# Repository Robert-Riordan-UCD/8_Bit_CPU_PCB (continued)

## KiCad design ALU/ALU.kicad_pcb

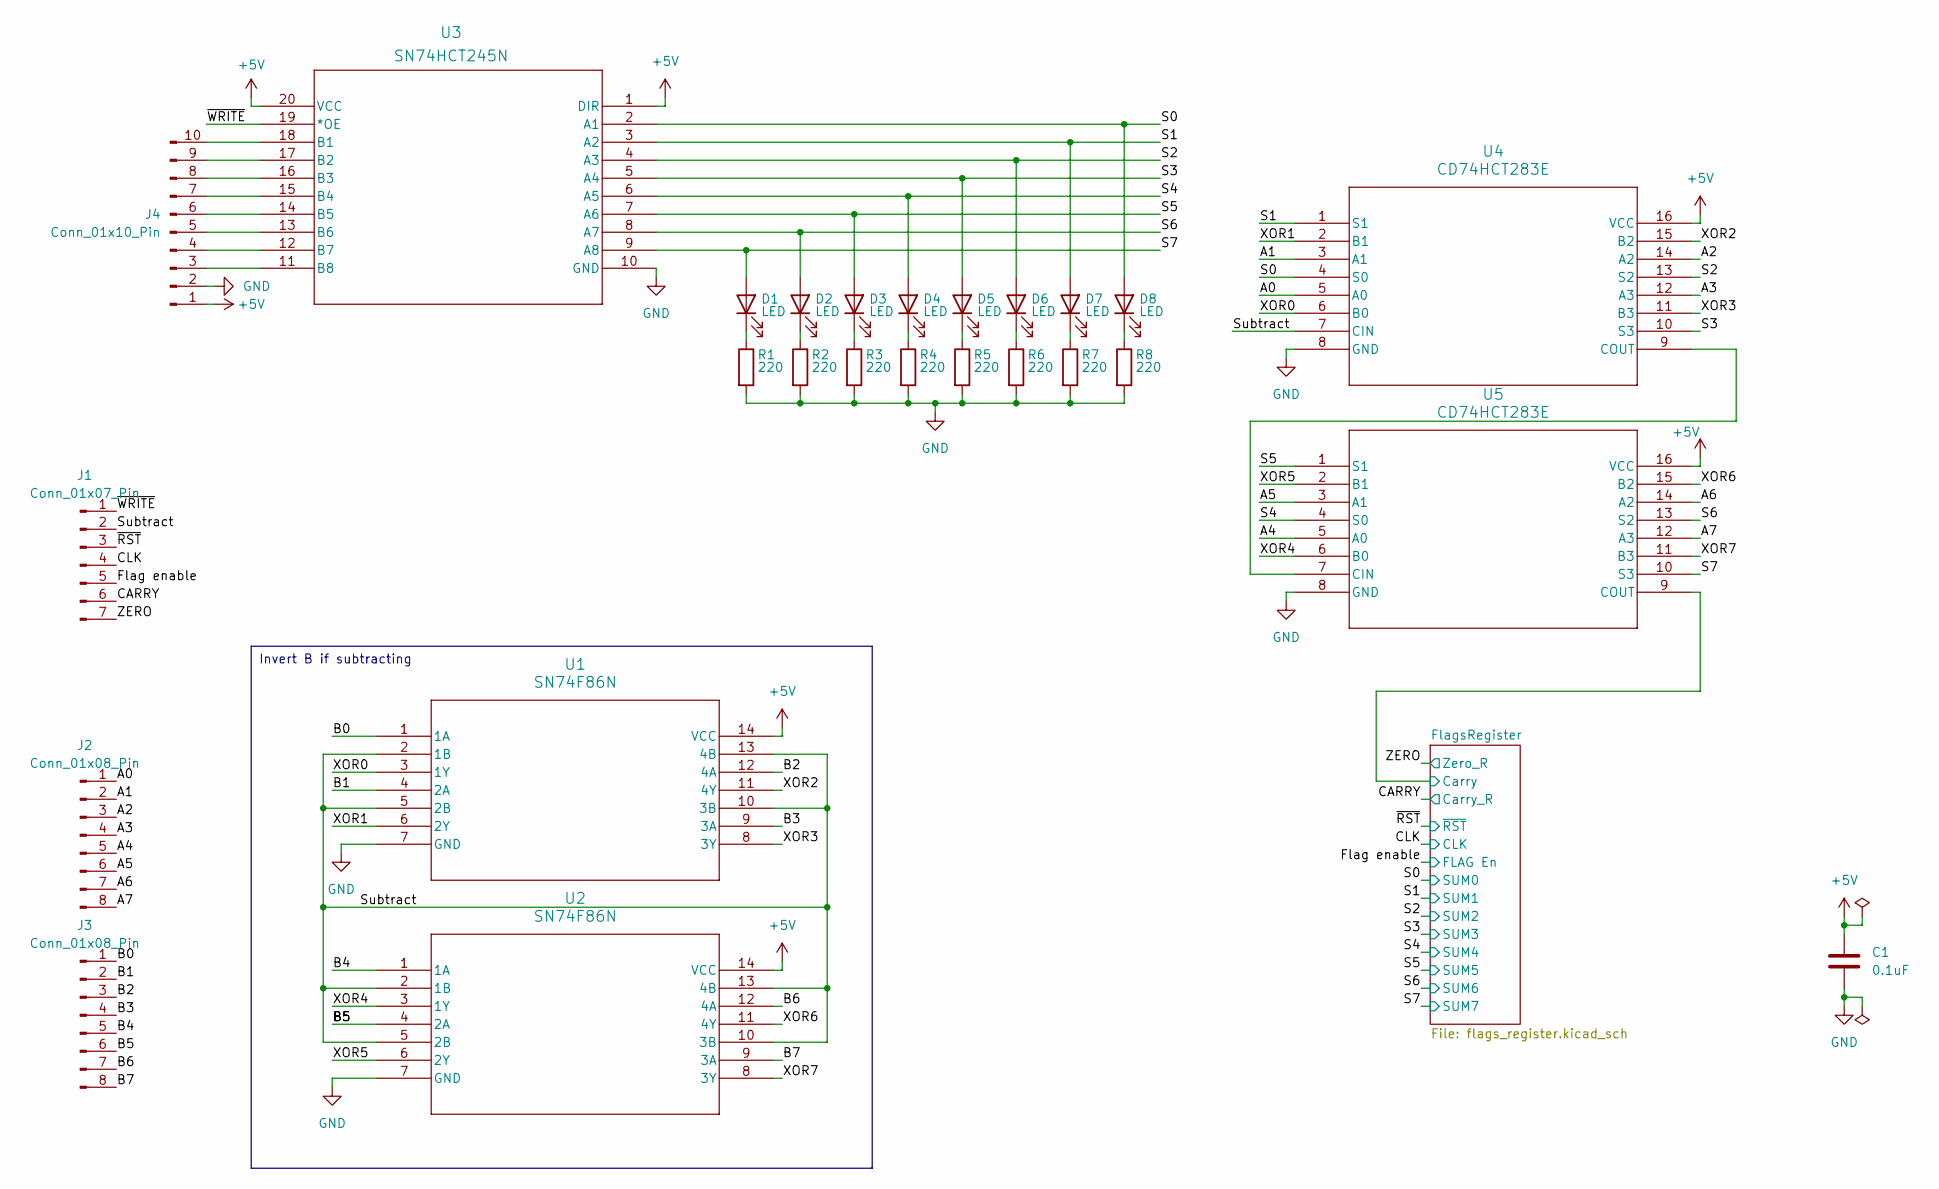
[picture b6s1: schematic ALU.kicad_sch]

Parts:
C1: 0.1uF; C_Disc_D5.0mm_W2.5mm_P2.50mm
D1, D2, D3, D4, D5, D6, D7, D8: LED; LED_D5.0mm
J1: Conn_01x07_Pin; PinHeader_1x07_P2.54mm_Vertical
J2, J3: Conn_01x08_Pin; PinHeader_1x08_P2.54mm_Vertical
J4: Conn_01x10_Pin; PinHeader_1x10_P2.54mm_Vertical
R1, R2, R3, R4, R5, R6, R7, R8: 220; CF_series_Resistors_THT
U1, U2: SN74F86N; 4x_xor
U3: SN74HCT245N; 8x_tristate_transceiver
U4, U5: CD74HCT283E; 4bit_full_adder

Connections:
+5V: C1.1, J4.1, U1.14 (VCC), U2.14 (VCC), U3.1 (DIR), U3.20 (VCC), U4.16 (VCC), U5.16 (VCC); also elsewhere on the board
/A0: J2.1, U4.5 (A0)
/A1: J2.2, U4.3 (A1)
/A2: J2.3, U4.14 (A2)
/A3: J2.4, U4.12 (A3)
/A4: J2.5, U5.5 (A0)
/A5: J2.6, U5.3 (A1)
/A6: J2.7, U5.14 (A2)
/A7: J2.8, U5.12 (A3)
/B0: J3.1, U1.1 (1A)
/B1: J3.2, U1.4 (2A)
/B2: J3.3, U1.12 (4A)
/B3: J3.4, U1.9 (3A)
/B4: J3.5, U2.1 (1A)
/B5: J3.6, U2.4 (2A)
/B6: J3.7, U2.12 (4A)
/B7: J3.8, U2.9 (3A)
/CARRY: J1.6; also elsewhere on the board
/CLK: J1.4; also elsewhere on the board
/Flag enable: J1.5; also elsewhere on the board
/FlagsRegister/Carry: U5.9 (COUT); also elsewhere on the board
/S0: D8.2 (A), U3.2 (A1), U4.4 (S0); also elsewhere on the board
/S1: D7.2 (A), U3.3 (A2), U4.1 (S1); also elsewhere on the board
/S2: D6.2 (A), U3.4 (A3), U4.13 (S2); also elsewhere on the board
/S3: D5.2 (A), U3.5 (A4), U4.10 (S3); also elsewhere on the board
/S4: D4.2 (A), U3.6 (A5), U5.4 (S0); also elsewhere on the board
/S5: D3.2 (A), U3.7 (A6), U5.1 (S1); also elsewhere on the board
/S6: D2.2 (A), U3.8 (A7), U5.13 (S2); also elsewhere on the board
/S7: D1.2 (A), U3.9 (A8), U5.10 (S3); also elsewhere on the board
/Subtract: J1.2, U1.2 (1B), U1.5 (2B), U1.10 (3B), U1.13 (4B), U2.2 (1B), U2.5 (2B), U2.10 (3B), U2.13 (4B), U4.7 (CIN)
/XOR0: U1.3 (1Y), U4.6 (B0)
/XOR1: U1.6 (2Y), U4.2 (B1)
/XOR2: U1.11 (4Y), U4.15 (B2)
/XOR3: U1.8 (3Y), U4.11 (B3)
/XOR4: U2.3 (1Y), U5.6 (B0)
/XOR5: U2.6 (2Y), U5.2 (B1)
/XOR6: U2.11 (4Y), U5.15 (B2)
/XOR7: U2.8 (3Y), U5.11 (B3)
/ZERO: J1.7; also elsewhere on the board
/~RST: J1.3; also elsewhere on the board
/~WRITE: J1.1, U3.19 (*OE)
GND: C1.2, J4.2, R1.2, R2.2, R3.2, R4.2, R5.2, R6.2, R7.2, R8.2, U1.7 (GND), U2.7 (GND), U3.10 (GND), U4.8 (GND), U5.8 (GND); also elsewhere on the board
unnamed: D1.1 (K), R1.1
unnamed: D2.1 (K), R2.1
unnamed: D3.1 (K), R3.1
unnamed: D4.1 (K), R4.1
unnamed: D5.1 (K), R5.1
unnamed: D6.1 (K), R6.1
unnamed: D7.1 (K), R7.1
unnamed: D8.1 (K), R8.1
unnamed: J4.3, U3.11 (B8)
unnamed: J4.4, U3.12 (B7)
unnamed: J4.5, U3.13 (B6)
unnamed: J4.6, U3.14 (B5)
unnamed: J4.7, U3.15 (B4)
unnamed: J4.8, U3.16 (B3)
unnamed: J4.9, U3.17 (B2)
unnamed: J4.10, U3.18 (B1)
unnamed: U4.9 (COUT), U5.7 (CIN)

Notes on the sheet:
Invert B if subtracting

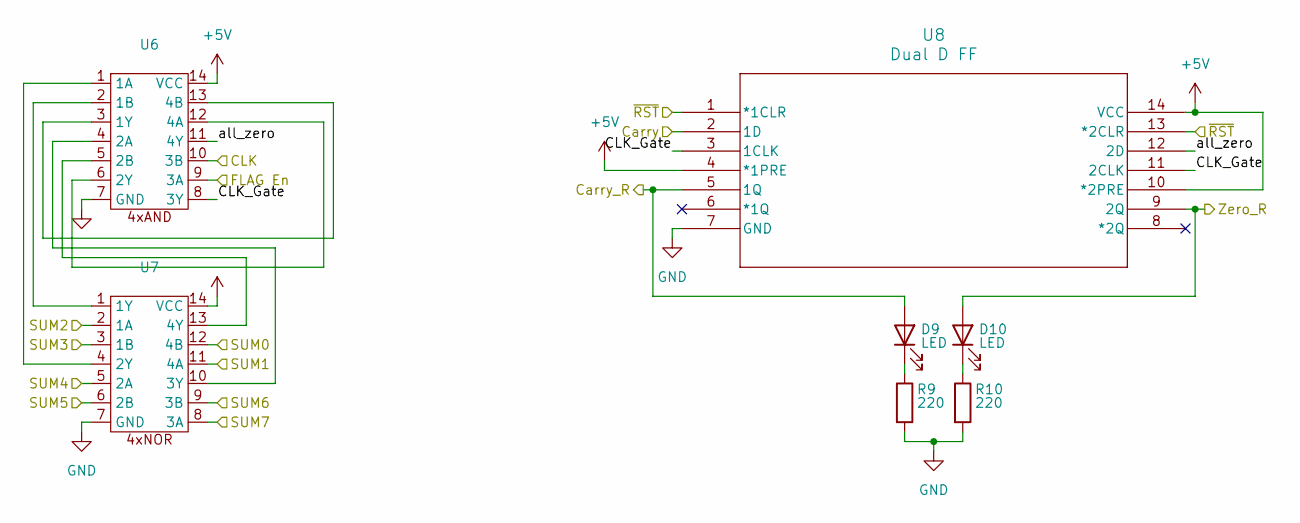
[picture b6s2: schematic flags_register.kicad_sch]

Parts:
D9, D10: LED; LED_D5.0mm
R9, R10: 220; CF_series_Resistors_THT
U6: 4x_and
U7: DIP-14_W7.62mm
U8: Dual D FF; 2x_D_FF

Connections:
+5V: U6.14 (VCC), U7.14 (VCC), U8.4 (*1PRE), U8.10 (*2PRE), U8.14 (VCC); also elsewhere on the board
/CARRY: D9.2 (A), U8.5 (1Q); also elsewhere on the board
/CLK: U6.10 (3B); also elsewhere on the board
/Flag enable: U6.9 (3A); also elsewhere on the board
/FlagsRegister/CLK_Gate: U6.8 (3Y), U8.3 (1CLK), U8.11 (2CLK)
/FlagsRegister/Carry: U8.2 (1D); also elsewhere on the board
/FlagsRegister/all_zero: U6.11 (4Y), U8.12 (2D)
/S0: U7.12 (4B); also elsewhere on the board
/S1: U7.11 (4A); also elsewhere on the board
/S2: U7.2 (1A); also elsewhere on the board
/S3: U7.3 (1B); also elsewhere on the board
/S4: U7.5 (2A); also elsewhere on the board
/S5: U7.6 (2B); also elsewhere on the board
/S6: U7.9 (3B); also elsewhere on the board
/S7: U7.8 (3A); also elsewhere on the board
/ZERO: D10.2 (A), U8.9 (2Q); also elsewhere on the board
/~RST: U8.1 (*1CLR), U8.13 (*2CLR); also elsewhere on the board
GND: R9.2, R10.2, U6.7 (GND), U7.7 (GND), U8.7 (GND); also elsewhere on the board
unnamed: D9.1 (K), R9.1
unnamed: D10.1 (K), R10.1
unnamed: U6.1 (1A), U7.4 (2Y)
unnamed: U6.2 (1B), U7.1 (1Y)
unnamed: U6.3 (1Y), U6.13 (4B)
unnamed: U6.4 (2A), U7.10 (3Y)
unnamed: U6.5 (2B), U7.13 (4Y)
unnamed: U6.6 (2Y), U6.12 (4A)

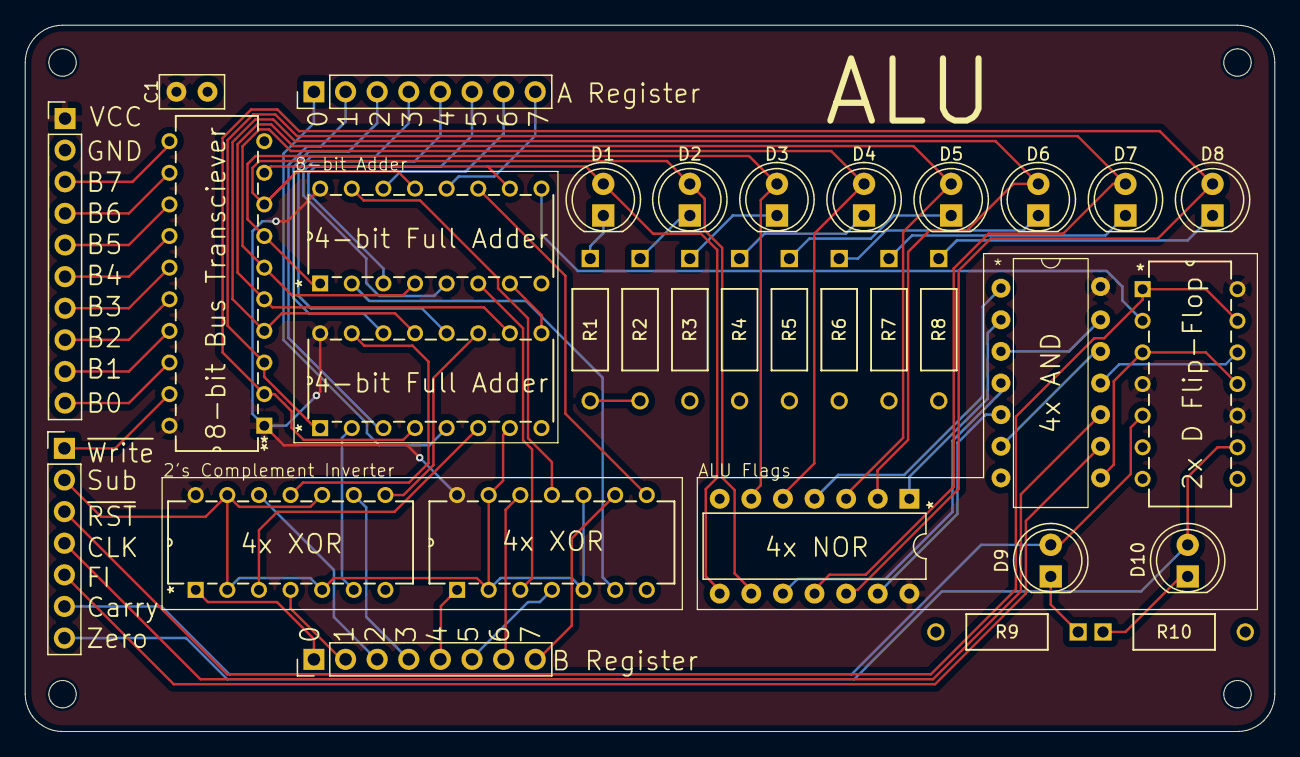
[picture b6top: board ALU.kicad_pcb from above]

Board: 2 copper layers, 100.4 x 56.8 mm, 33 parts (0 on the bottom side), 69 nets.

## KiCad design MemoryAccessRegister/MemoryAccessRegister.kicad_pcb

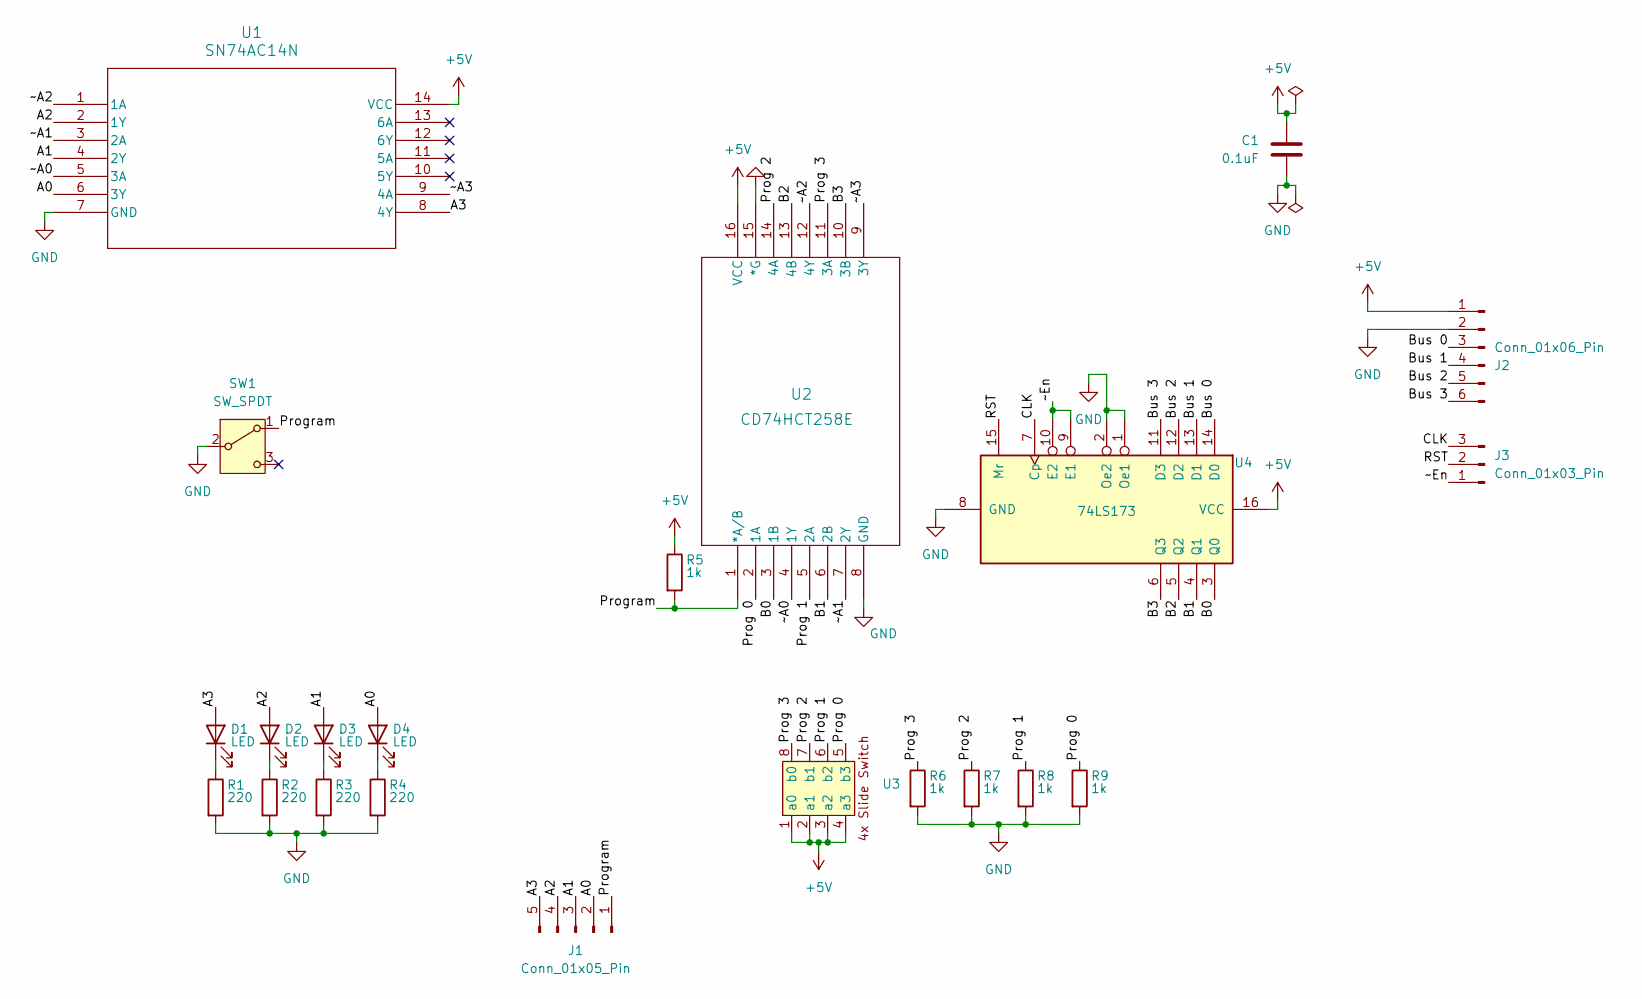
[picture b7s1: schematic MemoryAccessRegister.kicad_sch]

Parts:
C1: 0.1uF; C_Disc_D5.0mm_W2.5mm_P2.50mm
D1, D2, D3, D4: LED; LED_D5.0mm
J1: Conn_01x05_Pin; PinHeader_1x05_P2.54mm_Vertical
J2: Conn_01x06_Pin; PinHeader_1x06_P2.54mm_Vertical
J3: Conn_01x03_Pin; PinHeader_1x03_P2.54mm_Vertical
R1, R2, R3, R4: 220; CF_series_Resistors_THT
R5, R6, R7, R8, R9: 1k; CF_series_Resistors_THT
SW1: SW_SPDT; DoubleThrowSwitch
U1: SN74AC14N; 6x_not
U2: CD74HCT258E; 2_to_1_selector
U3: DIP-8
U4: 74LS173; DIP-16_W7.62mm

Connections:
+5V: C1.1, J2.1, R5.1, U1.14 (VCC), U2.16 (VCC), U3.1 (a0), U3.2 (a1), U3.3 (a2), U3.4 (a3), U4.16 (VCC)
/A0: D4.2 (A), J1.2, U1.6 (3Y)
/A1: D3.2 (A), J1.3, U1.4 (2Y)
/A2: D2.2 (A), J1.4, U1.2 (1Y)
/A3: D1.2 (A), J1.5, U1.8 (4Y)
/B0: U2.3 (1B), U4.3 (Q0)
/B1: U2.6 (2B), U4.4 (Q1)
/B2: U2.13 (4B), U4.5 (Q2)
/B3: U2.10 (3B), U4.6 (Q3)
/Bus 0: J2.3, U4.14 (D0)
/Bus 1: J2.4, U4.13 (D1)
/Bus 2: J2.5, U4.12 (D2)
/Bus 3: J2.6, U4.11 (D3)
/CLK: J3.3, U4.7 (Cp)
/Prog 0: R9.1, U2.2 (1A), U3.5 (b3)
/Prog 1: R8.1, U2.5 (2A), U3.6 (b2)
/Prog 2: R7.1, U2.14 (4A), U3.7 (b1)
/Prog 3: R6.1, U2.11 (3A), U3.8 (b0)
/Program: J1.1, R5.2, SW1.1 (A), U2.1 (*A/B)
/RST: J3.2, U4.15 (Mr)
/~A0: U1.5 (3A), U2.4 (1Y)
/~A1: U1.3 (2A), U2.7 (2Y)
/~A2: U1.1 (1A), U2.12 (4Y)
/~A3: U1.9 (4A), U2.9 (3Y)
/~En: J3.1, U4.9 (E1), U4.10 (E2)
GND: C1.2, J2.2, R1.2, R2.2, R3.2, R4.2, R6.2, R7.2, R8.2, R9.2, SW1.2 (B), U1.7 (GND), U2.8 (GND), U2.15 (*G), U4.1 (Oe1), U4.2 (Oe2), U4.8 (GND)
unnamed: D1.1 (K), R1.1
unnamed: D2.1 (K), R2.1
unnamed: D3.1 (K), R3.1
unnamed: D4.1 (K), R4.1

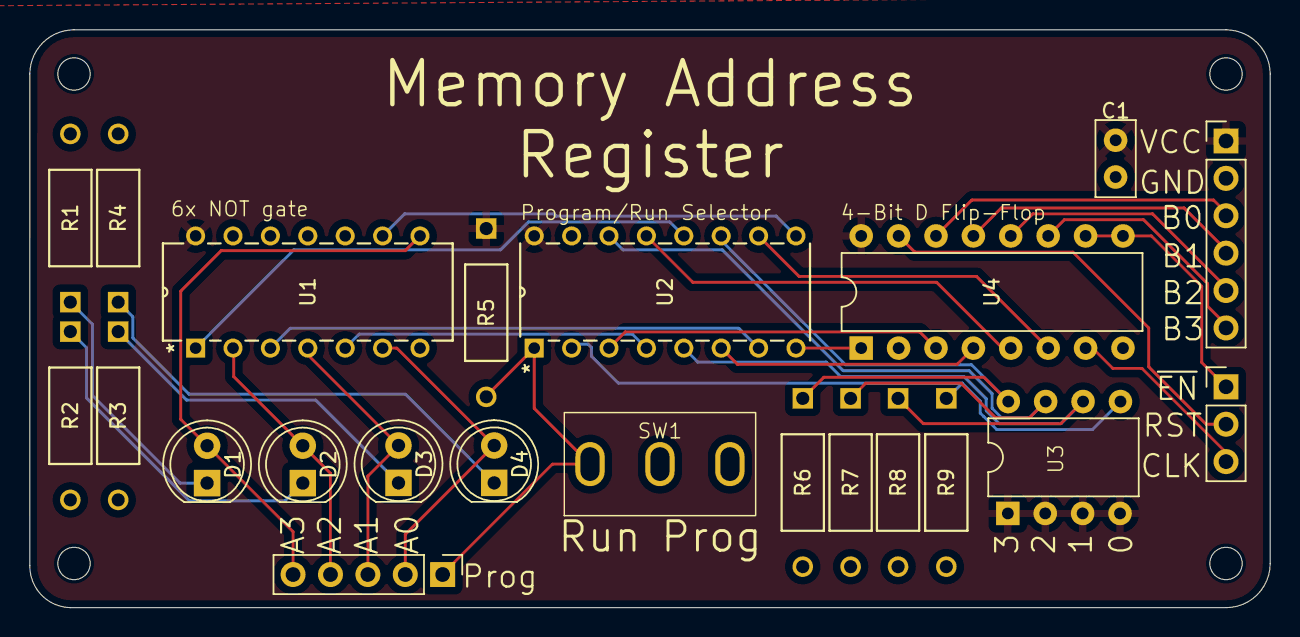
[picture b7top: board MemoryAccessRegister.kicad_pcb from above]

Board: 2 copper layers, 84.3 x 39.2 mm, 22 parts (0 on the bottom side), 30 nets.

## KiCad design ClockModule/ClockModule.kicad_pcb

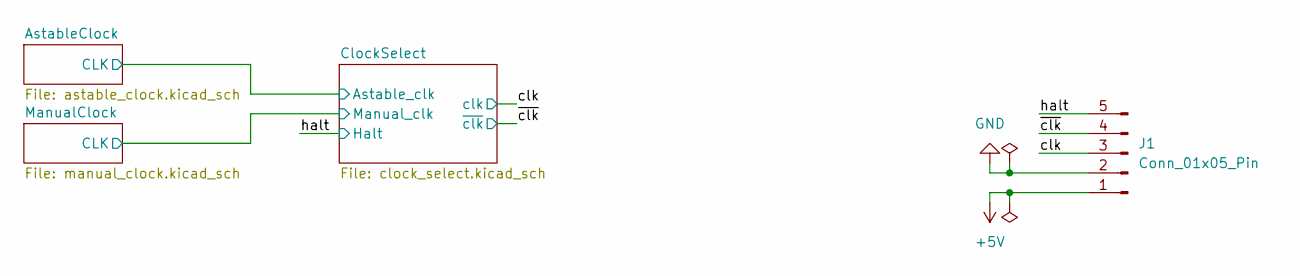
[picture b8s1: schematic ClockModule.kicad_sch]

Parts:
J1: Conn_01x05_Pin; PinHeader_1x05_P2.54mm_Vertical

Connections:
+5V: J1.1; also elsewhere on the board
/clk: J1.3; also elsewhere on the board
/halt: J1.5; also elsewhere on the board
/~clk: J1.4; also elsewhere on the board
GND: J1.2; also elsewhere on the board

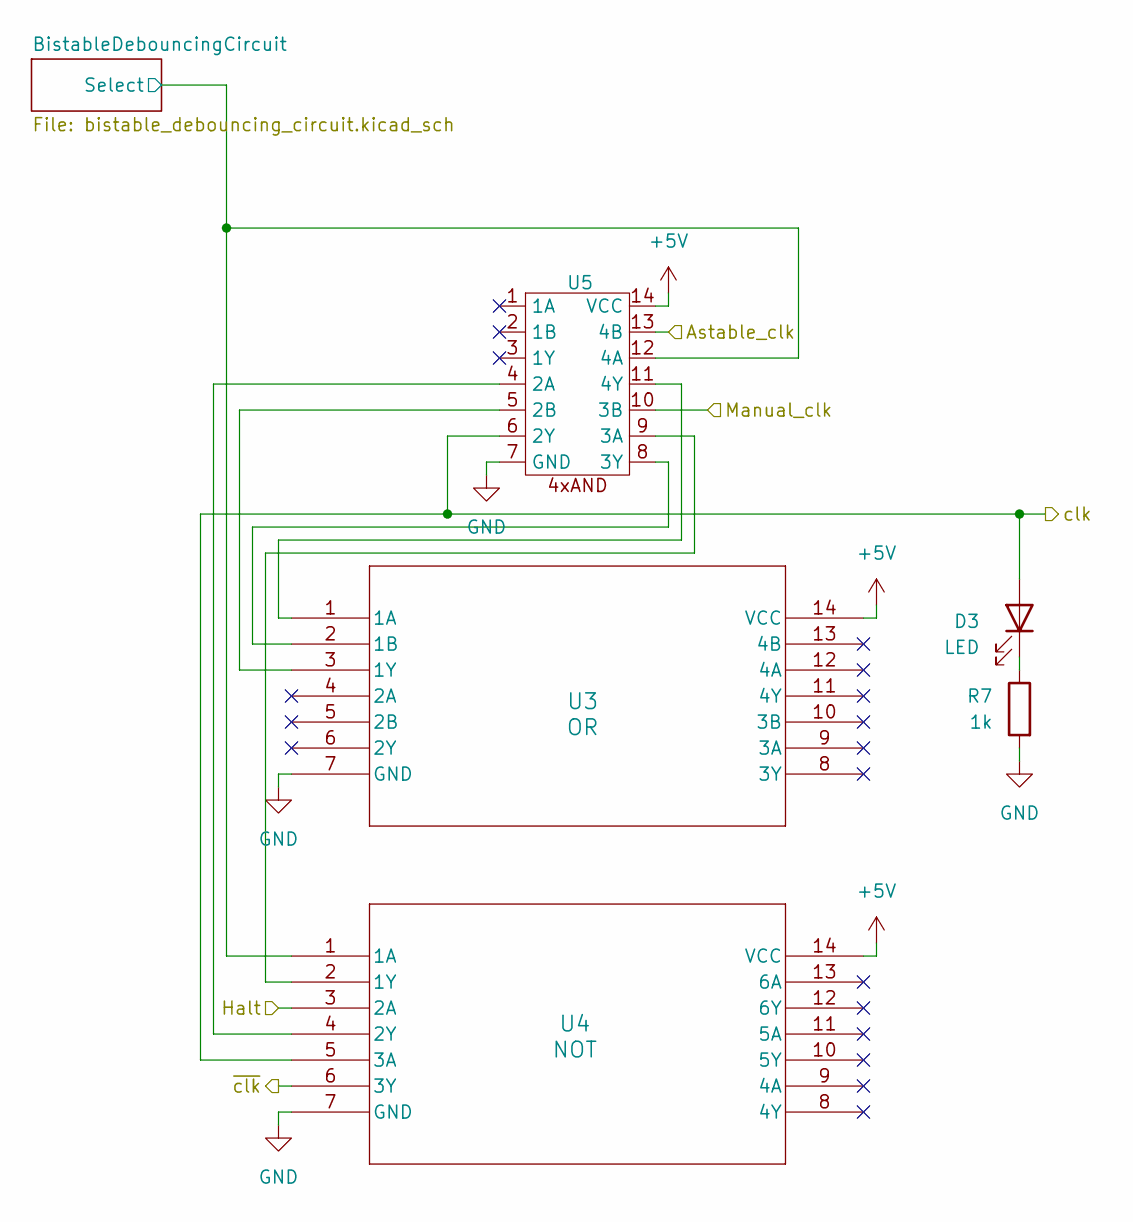
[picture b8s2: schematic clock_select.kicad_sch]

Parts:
D3: LED; LED_D5.0mm
R7: 1k; CF_series_Resistors_THT
U3: OR; 4x_or
U4: NOT; 6x_not
U5: 4x_and

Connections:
+5V: U3.14 (VCC), U4.14 (VCC), U5.14 (VCC); also elsewhere on the board
/AstableClock/CLK: U5.13 (4B); also elsewhere on the board
/ClockSelect/BistableDebouncingCircuit/Select: U4.1 (1A), U5.12 (4A); also elsewhere on the board
/ClockSelect/Manual_clk: U5.10 (3B); also elsewhere on the board
/clk: D3.2 (A), U4.5 (3A), U5.6 (2Y); also elsewhere on the board
/halt: U4.3 (2A); also elsewhere on the board
/~clk: U4.6 (3Y); also elsewhere on the board
GND: R7.2, U3.7 (GND), U4.7 (GND), U5.7 (GND); also elsewhere on the board
unnamed: D3.1 (K), R7.1
unnamed: U3.1 (1A), U5.11 (4Y)
unnamed: U3.2 (1B), U5.8 (3Y)
unnamed: U3.3 (1Y), U5.5 (2B)
unnamed: U4.2 (1Y), U5.9 (3A)
unnamed: U4.4 (2Y), U5.4 (2A)

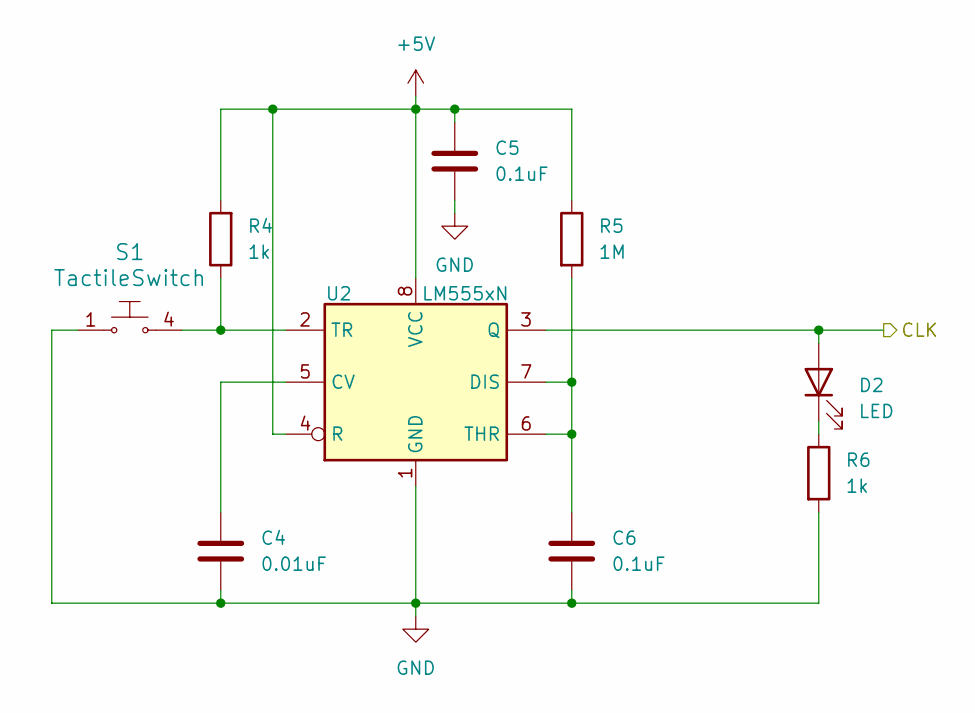
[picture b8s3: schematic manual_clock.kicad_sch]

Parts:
C4: 0.01uF; C_Disc_D5.0mm_W2.5mm_P2.50mm
C5, C6: 0.1uF; C_Disc_D5.0mm_W2.5mm_P2.50mm
D2: LED; LED_D5.0mm
R4, R6: 1k; CF_series_Resistors_THT
R5: 1M; CF_series_Resistors_THT
S1: TactileSwitch; tactile_switch; MPN B3U-1000P; Digi-Key_PN SW1020CT-ND
U2: LM555xN; DIP-8_W7.62mm

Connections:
+5V: C5.1, R4.2, R5.1, U2.4 (R), U2.8 (VCC); also elsewhere on the board
/ClockSelect/Manual_clk: D2.2 (A), U2.3 (Q); also elsewhere on the board
GND: C4.2, C5.2, C6.2, R6.2, S1.1, U2.1 (GND); also elsewhere on the board
unnamed: D2.1 (K), R6.1
unnamed: C4.1, U2.5 (CV)
unnamed: C6.1, R5.2, U2.6 (THR), U2.7 (DIS)
unnamed: R4.1, S1.4, U2.2 (TR)

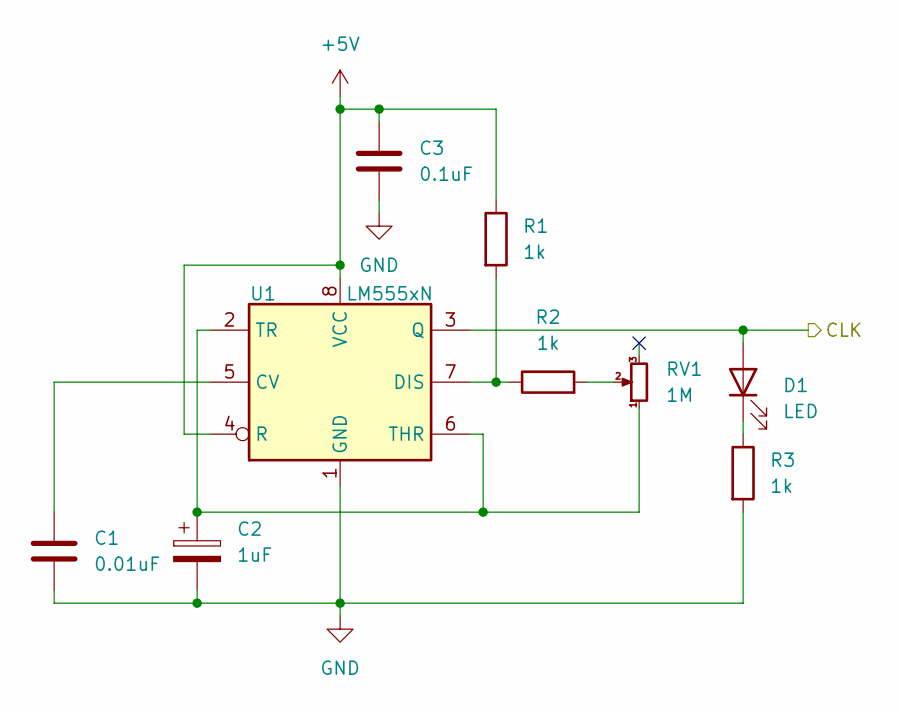
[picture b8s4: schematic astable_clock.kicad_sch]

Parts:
C1: 0.01uF; C_Disc_D5.0mm_W2.5mm_P2.50mm
C2: 1uF; Cp_2mm_pin_spacing
C3: 0.1uF; C_Disc_D5.0mm_W2.5mm_P2.50mm
D1: LED; LED_D5.0mm
R1, R2, R3: 1k; CF_series_Resistors_THT
RV1: 1M; R_var
U1: LM555xN; DIP-8_W7.62mm

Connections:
+5V: C3.1, R1.1, U1.4 (R), U1.8 (VCC); also elsewhere on the board
/AstableClock/CLK: D1.2 (A), U1.3 (Q); also elsewhere on the board
GND: C1.2, C2.2, C3.2, R3.2, U1.1 (GND); also elsewhere on the board
unnamed: D1.1 (K), R3.1
unnamed: R2.2, RV1.2
unnamed: C1.1, U1.5 (CV)
unnamed: R1.2, R2.1, U1.7 (DIS)
unnamed: C2.1, RV1.1, U1.2 (TR), U1.6 (THR)

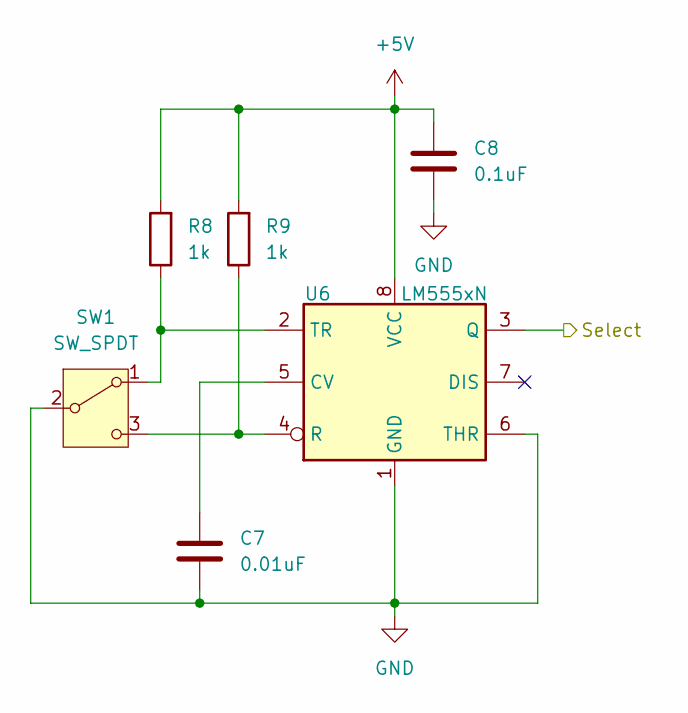
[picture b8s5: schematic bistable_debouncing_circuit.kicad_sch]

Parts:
C7: 0.01uF; C_Disc_D5.0mm_W2.5mm_P2.50mm
C8: 0.1uF; C_Disc_D5.0mm_W2.5mm_P2.50mm
R8, R9: 1k; CF_series_Resistors_THT
SW1: SW_SPDT; DoubleThrowSwitch
U6: LM555xN; DIP-8_W7.62mm

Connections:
+5V: C8.1, R8.2, R9.2, U6.8 (VCC); also elsewhere on the board
/ClockSelect/BistableDebouncingCircuit/Select: U6.3 (Q); also elsewhere on the board
GND: C7.2, C8.2, SW1.2 (B), U6.1 (GND), U6.6 (THR); also elsewhere on the board
unnamed: R8.1, SW1.1 (A), U6.2 (TR)
unnamed: R9.1, SW1.3 (C), U6.4 (R)
unnamed: C7.1, U6.5 (CV)

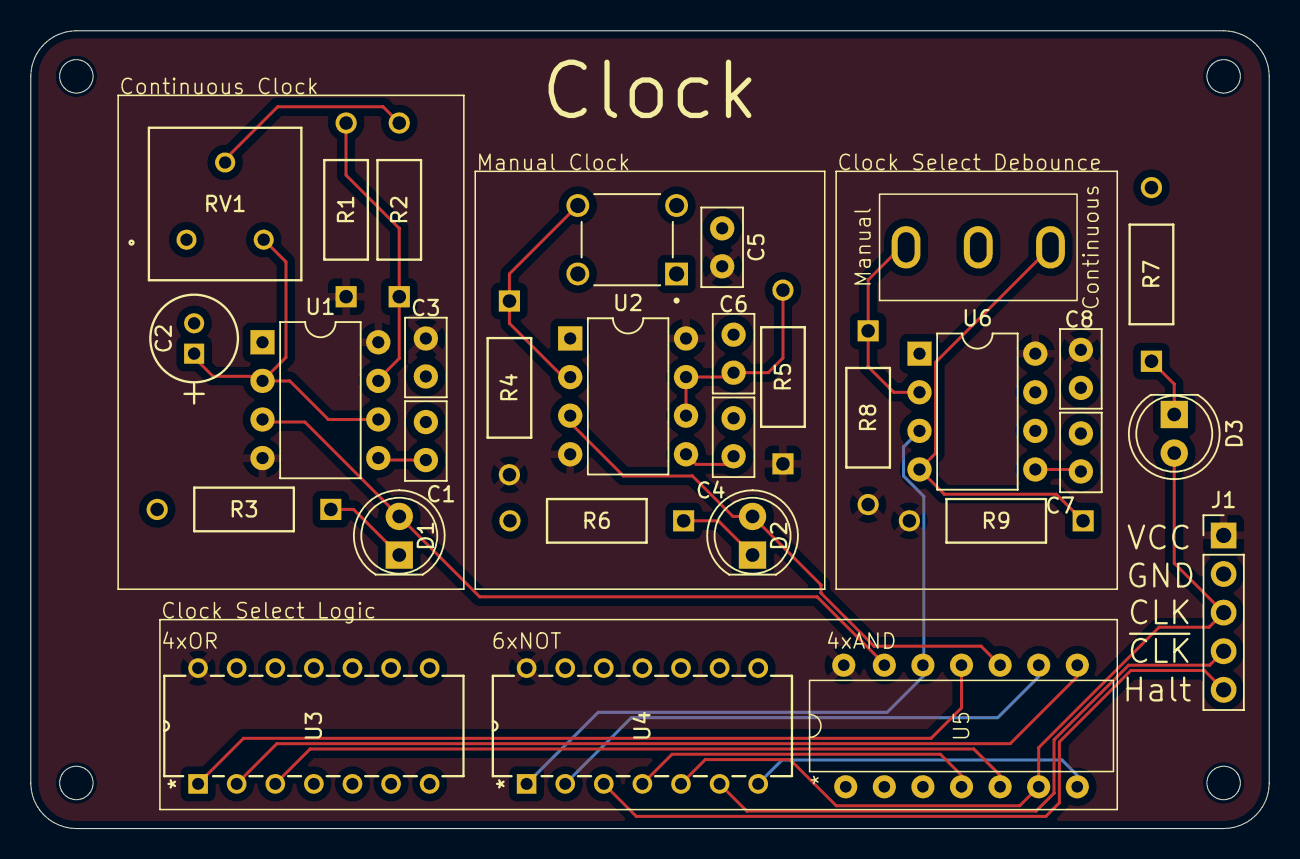
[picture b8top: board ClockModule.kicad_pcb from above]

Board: 2 copper layers, 81.5 x 52.5 mm, 30 parts (0 on the bottom side), 26 nets.

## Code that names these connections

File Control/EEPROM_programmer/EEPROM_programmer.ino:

#define SHIFT_DATA 2
#define SHIFT_CLK 3
#define SHIFT_LATCH 4

#define WRITE_EN_N 13

#define NUM_IO 8
int IO_PINS[8] = {5, 6, 7, 8, 9, 10, 11, 12};
// Address pin uses
#define ZERO       0
#define CARRY      1
#define T2         2
#define T1         3
#define T0         4
#define EEPROM_SEL 5
#define SPARE0     6
#define SPARE1     7
#define IR4        8
#define IR5        9
#define IR7        10
#define IR6        11
#define SPARE2     12

#define ADDRESS_SIZE 13

// Control signals
#define PCO     0b0000000000000001
#define ALU_SUB 0b0000000000000010
#define ALU_FI  0b0000000000000100
#define PC_JMP  0b0000000000001000
#define CLK_HLT 0b0000000000010000
#define PCE     0b0000000000100000
#define AI      0b0000000001000000
#define AO      0b0000000010000000

#define OUT_EN  0b0000000100000000
#define BI      0b0000001000000000
#define ALU_OUT 0b0000010000000000
#define IO      0b0000100000000000
#define II      0b0001000000000000
#define RI      0b0010000000000000
#define RO      0b0100000000000000
#define MI      0b1000000000000000

// Fetch cycle
#define FETCH   MI|PCO, RO|II|PCE

// Instruction set
#define NOOP { FETCH,         0,                         0, 0, 0, 0, 0}
#define LDA  { FETCH,     IO|MI,                     RO|AI, 0, 0, 0, 0}
#define STA  { FETCH,     IO|MI,                     AO|RI, 0, 0, 0, 0}
#define LDB  { FETCH,     IO|MI,                     RO|BI, 0, 0, 0, 0}
#define ADD  { FETCH,     IO|MI,         ALU_OUT|AI|ALU_FI, 0, 0, 0, 0}
#define SUB  { FETCH,     IO|MI, ALU_OUT|ALU_SUB|AI|ALU_FI, 0, 0, 0, 0}
#define JMP  { FETCH, IO|PC_JMP,                         0, 0, 0, 0, 0}
#define OUT  { FETCH, AO|OUT_EN,                         0, 0, 0, 0, 0}
#define HALT { FETCH,   CLK_HLT,                         0, 0, 0, 0, 0}
#define JMP_CARRY_FALSE NOOP
#define JMP_CARRY_TRUE  JMP
#define JMP_ZERO_FALSE  NOOP
#define JMP_ZERO_TRUE   JMP

const uint16_t code[4][16][8] = {
  {NOOP, LDA, STA, LDB, ADD, SUB, JMP, JMP_CARRY_FALSE, JMP_ZERO_FALSE, NOOP, NOOP, NOOP, NOOP, NOOP, OUT, HALT}, // Zero = 0, Carry = 0
  {NOOP, LDA, STA, LDB, ADD, SUB, JMP, JMP_CARRY_FALSE,  JMP_ZERO_TRUE, NOOP, NOOP, NOOP, NOOP, NOOP, OUT, HALT}, // Zero = 0, Carry = 1
  {NOOP, LDA, STA, LDB, ADD, SUB, JMP,  JMP_CARRY_TRUE, JMP_ZERO_FALSE, NOOP, NOOP, NOOP, NOOP, NOOP, OUT, HALT}, // Zero = 1, Carry = 0
  {NOOP, LDA, STA, LDB, ADD, SUB, JMP,  JMP_CARRY_TRUE,  JMP_ZERO_TRUE, NOOP, NOOP, NOOP, NOOP, NOOP, OUT, HALT}  // Zero = 1, Carry = 1
};

const int rom_size = pow(2, ADDRESS_SIZE);

void setAddress(uint16_t address, bool output_enable) {
  digitalWrite(SHIFT_LATCH, LOW);

  shiftOut(SHIFT_DATA, SHIFT_CLK, MSBFIRST, address>>8 | (output_enable ? 0 : 0b10000000));
  shiftOut(SHIFT_DATA, SHIFT_CLK, MSBFIRST, address);

  digitalWrite(SHIFT_LATCH, HIGH);
  digitalWrite(SHIFT_LATCH, LOW);
}

uint8_t readEEPROM(uint16_t address) {
  setAddress(address, true);
  
  uint8_t data = 0;
  for (int i = NUM_IO-1; i >= 0; i--) {
    pinMode(IO_PINS[i], INPUT);
    data = (data<<1) + digitalRead(IO_PINS[i]);
  }

  return data;
}

void writeEEPROM(uint16_t address, uint8_t data) {
  digitalWrite(WRITE_EN_N, HIGH);
  setAddress(address, false);

  for (int i = 0; i < NUM_IO; i++) {
    pinMode(IO_PINS[i], OUTPUT);
    digitalWrite(IO_PINS[i], (data>>i)&1);
  }

  digitalWrite(WRITE_EN_N, LOW);
  delayMicroseconds(1);
  digitalWrite(WRITE_EN_N, HIGH);
  delay(15);
}

void setup() {
  Serial.begin(9600);
  Serial.println();
  
  pinMode(SHIFT_DATA, OUTPUT);
  pinMode(SHIFT_CLK, OUTPUT);
  pinMode(SHIFT_LATCH, OUTPUT);

  digitalWrite(WRITE_EN_N, HIGH);
  pinMode(WRITE_EN_N, OUTPUT);

  Serial.println("Addr: Flags, Inst, Step, Control, Boot");
  for (int address = 0; address < rom_size; address++) {
    uint8_t bootload = (
      (((address>>SPARE1)&1) << 1) |
      (((address>>SPARE0)&1) << 0)
    );
    
    uint8_t flags = (
      (((address>>CARRY)&1) << 0) |
      (((address>>ZERO )&1) << 1)
    );
    
    uint8_t instruction = (
      (((address>>IR4)&1) << 0) |
      (((address>>IR5)&1) << 1) |
      (((address>>IR6)&1) << 2) |
      (((address>>IR7)&1) << 3)
    );

    uint8_t step = (
      (((address>>T0)&1) << 0) |
      (((address>>T1)&1) << 1) |
      (((address>>T2)&1) << 2)
    );

    char buffer[100];
    sprintf(buffer, "0x%03x:    %d, 0x%01x,    %d,  0x%04x, 0x%01x",
                     address, flags, instruction, step, code[flags][instruction][step], bootload);
    Serial.println(buffer);

    switch (bootload) {
      case 0b00:
        if ((address>>EEPROM_SEL)&1) {
          writeEEPROM(address, code[flags][instruction][step]);
        } else {
          writeEEPROM(address, code[flags][instruction][step]>>8);
        }
        break;
      case 0b01: writeEEPROM(address, MI); break;
      case 0b10: writeEEPROM(address, RI); break;
      case 0b11: writeEEPROM(address, 0); break;
    }
  }

  // NOTE: First bit read after a write is usually wrong so reading now to clear the issue
  readEEPROM(0);

  for (int i = 0; i < rom_size; i++) {
    uint8_t data = readEEPROM(i);
    if (data < 0x10) {
      Serial.print('0');
      Serial.print(data, HEX);      
    } else {
      Serial.print(data, HEX);
    }
    Serial.print(' ');
    if ((i+1)%16 == 0) {
      Serial.println();
    }
  }
}

void loop() {}

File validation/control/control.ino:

/* TEST PLAN
 *
 * 1) Test each instruction
 *  a) Check each step though the microcode cycle
 *  b) Check with all flag states
 */
#define DEBUG false

#define CLK_HALF_PERIOD_MS 20

// Control output pins
#define I_WO_N   37
#define I_RI_N   35
#define RAM_RI   33
#define RAM_WO_N 31
#define MAR_EN_N 29
#define CLK_HALT 27
#define PC_JMP_N 25
#define PC_EN    23

#define PC_CO_N  36
#define A_WO_N   34
#define A_RI_N   32
#define ALU_WO_N 30
#define ALU_SUB  28
#define ALU_FI   26
#define B_RI_N   24
#define OUT_EN_N 22

#define RST 41

// Control input pins
#define ALU_CARRY 47
#define ALU_ZERO  45
#define CLK       43
#define INS_SIZE  4
const int instruction[INS_SIZE] = {44, 42, 40, 38};

// Signal bit mapping
#define IO   0x8000
#define II   0x4000
#define RI   0x2000
#define RO   0x1000
#define MI   0x0800
#define HLT  0x0400
#define JMP  0x0200
#define PCE  0x0100
#define PCO  0x0080
#define AO   0x0040
#define AI   0x0020
#define ALUO 0x0010
#define SUB  0x0008
#define FI   0x0004
#define BI   0x0002
#define OUT  0x0001

/* Basic utility functions */
void print_bin8(int n) {
  for(int i = 7; i >= 0; i--) {
    Serial.print((n>>i)&1);
  }
}

void print_signals(uint16_t signals) {
  if (signals & IO)   {Serial.print("IR OUT, ");}
  if (signals & II)   {Serial.print("IR IN, ");}
  if (signals & RI)   {Serial.print("RAM IN, ");}
  if (signals & RO)   {Serial.print("RAM OUT, ");}
  if (signals & MI)   {Serial.print("MAR EN, ");}
  if (signals & HLT)  {Serial.print("CLK HLT, ");}
  if (signals & JMP)  {Serial.print("JMP, ");}
  if (signals & PCE)  {Serial.print("PC EN, ");}
  
  if (signals & PCO)  {Serial.print("PC OUT, ");}
  if (signals & AO)   {Serial.print("AR OUT, ");}
  if (signals & AI)   {Serial.print("AR IN, ");}
  if (signals & ALUO) {Serial.print("ALU OUT, ");}
  if (signals & SUB)  {Serial.print("ALU SUB, ");}
  if (signals & FI)   {Serial.print("ALU FI, ");}
  if (signals & BI)   {Serial.print("BR IN, ");}
  if (signals & OUT)  {Serial.print("OUT EN, ");}
}

bool test_equal(int value, int expected, char* test) {
  if (value == expected) {
    if (DEBUG == false) {return true;}
    Serial.print("Pass  (");
    Serial.print(test);
    Serial.print("): Expected ");
    Serial.print(expected);
    Serial.print(" (");
    print_signals(expected);
    Serial.print(")");
    Serial.print(" - Actual ");
    Serial.print(value);
    Serial.print(" (");
    print_signals(value);
    Serial.print(")");
    Serial.println();
    return true;
  } else {
    Serial.print("ERROR (");
    Serial.print(test);
    Serial.print("): Expected ");
    Serial.print(expected);
    Serial.print(" (");
    print_signals(expected);
    Serial.print(")");
    Serial.print(" - Actual ");
    Serial.print(value);
    Serial.print(" (");
    print_signals(value);
    Serial.print(")");
    Serial.println();
    return false;
  }
}

void clock_pulse() {
  digitalWrite(CLK, HIGH);
  delay(CLK_HALF_PERIOD_MS);
  digitalWrite(CLK, LOW);
  delay(CLK_HALF_PERIOD_MS);
}

uint16_t read_control_signals() {
  uint16_t state = 0;
  state += !digitalRead(I_WO_N);
  state <<= 1;
  state += !digitalRead(I_RI_N);
  state <<= 1;
  state += digitalRead(RAM_RI);
  state <<= 1;
  state += !digitalRead(RAM_WO_N);
  state <<= 1;
  state += !digitalRead(MAR_EN_N);
  state <<= 1;
  state += digitalRead(CLK_HALT);
  state <<= 1;
  state += !digitalRead(PC_JMP_N);
  state <<= 1;
  state += digitalRead(PC_EN);
  state <<= 1;
  
  state += !digitalRead(PC_CO_N);
  state <<= 1;
  state += !digitalRead(A_WO_N);
  state <<= 1;
  state += !digitalRead(A_RI_N);
  state <<= 1;
  state += !digitalRead(ALU_WO_N);
  state <<= 1;
  state += digitalRead(ALU_SUB);
  state <<= 1;
  state += digitalRead(ALU_FI);
  state <<= 1;
  state += !digitalRead(B_RI_N);
  state <<= 1;
  state += !digitalRead(OUT_EN_N);

  return state;
}

void set_instruction(uint8_t ins) {
  for (int i=0; i<INS_SIZE; i++) {
    digitalWrite(instruction[i], (ins>>i)&1);
  }
}

// Get the user to press the reset button to reset the microcode timer
void reset_timer() {
  Serial.println("Please press reset");
  while(digitalRead(RST) == LOW) {}
  clock_pulse();
  while(digitalRead(RST) == HIGH) {}
}

/* Test functions */
int test_ins(uint8_t ins, uint16_t code[6], char *test_name) {
  int pass = 0;
  set_instruction(ins);
  for (uint8_t flags=0; flags<=3; flags++) {
    digitalWrite(ALU_CARRY, flags>>1);
    digitalWrite(ALU_ZERO, flags&1);
    for (int i=0; i<6; i++) {
      char buf[100];
      sprintf(buf, "%s (0x%x) T=%d (C=%d,Z=%d)", test_name, ins, i, (flags>>1)&1, flags&1);
      pass += test_equal(read_control_signals(), code[i], buf);
      clock_pulse();
    }
  }
  return pass;
}

int test_jmpc() {
  int pass = 0;
  uint16_t code_carry_set[6] = {MI|PCO, RO|II|PCE, IO|JMP, 0, 0, 0};
  uint16_t code_carry_not_set[6] = {MI|PCO, RO|II|PCE, 0, 0, 0, 0};
  set_instruction(0b0111);
  for (uint8_t flags=0; flags<=3; flags++) {
    digitalWrite(ALU_CARRY, flags>>1);
    digitalWrite(ALU_ZERO, flags&1);
    for (int i=0; i<6; i++) {
      char buf[100];
      sprintf(buf, "Jump Carry (0x0111) T=%d (C=%d,Z=%d)", i, (flags>>1)&1, flags&1);
      if (flags>>1) {
        pass += test_equal(read_control_signals(), code_carry_set[i], buf);
      } else {
        pass += test_equal(read_control_signals(), code_carry_not_set[i], buf);
      }
      clock_pulse();
    }
  }
  return pass;
}

int test_jmpz() {
  int pass = 0;
  uint16_t code_carry_set[6] = {MI|PCO, RO|II|PCE, IO|JMP, 0, 0, 0};
  uint16_t code_carry_not_set[6] = {MI|PCO, RO|II|PCE, 0, 0, 0, 0};
  set_instruction(0b1000);
  for (uint8_t flags=0; flags<=3; flags++) {
    digitalWrite(ALU_CARRY, flags>>1);
    digitalWrite(ALU_ZERO, flags&1);
    for (int i=0; i<6; i++) {
      char buf[100];
      sprintf(buf, "Jump Zero (0x1000) T=%d (C=%d,Z=%d)", i, (flags>>1)&1, flags&1);
      if (flags&1) {
        pass += test_equal(read_control_signals(), code_carry_set[i], buf);
      } else {
        pass += test_equal(read_control_signals(), code_carry_not_set[i], buf);
      }
      clock_pulse();
    }
  }
  return pass;
}

void setup() {
  Serial.begin(9600);

  /* Pin setup */
  pinMode(ALU_CARRY, OUTPUT);
  digitalWrite(ALU_CARRY, LOW);
  pinMode(ALU_ZERO, OUTPUT);
  digitalWrite(ALU_ZERO, LOW);
  pinMode(CLK, OUTPUT);
  digitalWrite(CLK, LOW);
  for (int ins=0; ins<pow(2, INS_SIZE); ins++) {
    pinMode(ins, OUTPUT);
    digitalWrite(ins, LOW);
  }

  pinMode(RST, INPUT);

  pinMode(I_WO_N, INPUT);
  pinMode(I_RI_N, INPUT);
  pinMode(RAM_RI, INPUT);
  pinMode(RAM_WO_N, INPUT);
  pinMode(MAR_EN_N, INPUT);
  pinMode(CLK_HALT, INPUT);
  pinMode(PC_JMP_N, INPUT);
  pinMode(PC_EN, INPUT);
  pinMode(PC_CO_N, INPUT);
  pinMode(A_WO_N, INPUT);
  pinMode(A_RI_N, INPUT);
  pinMode(ALU_WO_N, INPUT);
  pinMode(ALU_SUB, INPUT);
  pinMode(ALU_FI, INPUT);
  pinMode(B_RI_N, INPUT);
  pinMode(OUT_EN_N, INPUT);

  reset_timer();
  
  /* Tests */
  uint16_t code[][6] = {
    {MI|PCO, RO|II|PCE, 0, 0, 0, 0}, // No OP
    {MI|PCO, RO|II|PCE, IO|MI, RO|AI, 0, 0}, // LDA
    {MI|PCO, RO|II|PCE, IO|MI, RO|BI, ALUO|FI|AI, 0}, // ADD
    {MI|PCO, RO|II|PCE, IO|MI, RO|BI, ALUO|SUB|FI|AI, 0}, // SUB
    {MI|PCO, RO|II|PCE, IO|MI, AO|RI, 0, 0}, // STA
    {MI|PCO, RO|II|PCE, IO|AI, 0, 0, 0}, // LDI
    {MI|PCO, RO|II|PCE, IO|JMP, 0, 0, 0}, // JMP
    {MI|PCO, RO|II|PCE, AO|OUT, 0, 0, 0}, // OUT
    {MI|PCO, RO|II|PCE, HLT, 0, 0, 0} // HALT
  };
  int noop = test_ins(0, code[0], "No OP");
  int lda = test_ins(1, code[1], "Load A");
  int add = test_ins(2, code[2], "Add");
  int sub = test_ins(3, code[3], "Subtract");
  int sta = test_ins(4, code[4], "Store A");
  int ldi = test_ins(5, code[5], "Load imediate");
  int jmp = test_ins(6, code[6], "Jump");
  int out = test_ins(14, code[7], "Output");
  int hlt = test_ins(15, code[8], "Halt");
  int jmpc = test_jmpc();
  int jmpz = test_jmpz();

  Serial.print("No OP:\t\t");
  Serial.print(noop);
  Serial.println("/24");

  Serial.print("Load A:\t\t");
  Serial.print(lda);
  Serial.println("/24");

  Serial.print("Add:\t\t");
  Serial.print(add);
  Serial.println("/24");

  Serial.print("Subtract:\t");
  Serial.print(sub);
  Serial.println("/24");

  Serial.print("Store A:\t");
  Serial.print(sta);
  Serial.println("/24");

  Serial.print("Load Imediate:\t");
  Serial.print(ldi);
  Serial.println("/24");

  Serial.print("Jump:\t\t");
  Serial.print(jmp);
  Serial.println("/24");

  Serial.print("Output:\t\t");
  Serial.print(out);
  Serial.println("/24");

  Serial.print("Halt:\t\t");
  Serial.print(hlt);
  Serial.println("/24");

  Serial.print("Jump carry:\t");
  Serial.print(jmpc);
  Serial.println("/24");

  Serial.print("Jump zero:\t");
  Serial.print(jmpz);
  Serial.println("/24");
  
  Serial.println();
}

void loop() {}
